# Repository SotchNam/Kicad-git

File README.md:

# Github tools used:
- *[KiCad-Diff](https://github.com/Gasman2014/KiCad-Diff)*: Provides side by side visualisation of each layer of the pcb between two commits, unable to do schematics it seems.
- *[Kiri](https://github.com/leoheck/kiri)*: Usefull tool that allows to see visualize diff of everything, in a web browser. Based on KiCad-Diff
- *[KiDiff](https://github.com/INTI-CMNB/KiDiff)*: A git plugin, opens a pdf every ``git diff`` run that shows overlays of changes. Simple.
- *[Board2Pdf](https://gitlab.com/dennevi/Board2Pdf)*: Plugin to generate pdf export of pcb layout, had an issue with python PyMuPDF. Can be used on cli, which is usefull to make it a commit git hook or automate actions.
- *[kicad render pcb](https://github.com/marketplace/actions/kicad-render-pcb)*: Github action tat develops a render of the pcb.
### Images

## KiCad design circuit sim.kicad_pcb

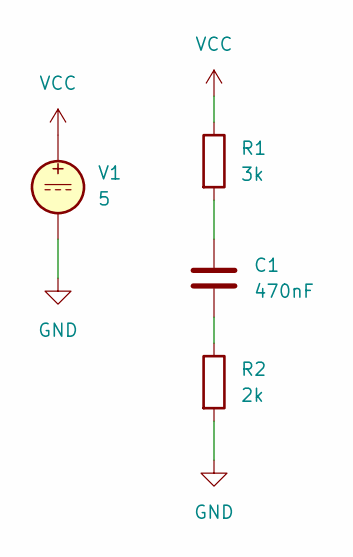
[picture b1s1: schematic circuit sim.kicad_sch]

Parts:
C1: 470nF; C_1206_3216Metric
R1: 3k; R_0603_1608Metric
R2: 2k; R_0603_1608Metric
V1: 5; PinHeader_1x02_P1.00mm_Vertical

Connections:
GND: R2.2, V1.2
unnamed: C1.1, R1.2
unnamed: C1.2, R2.1
VCC: R1.1, V1.1

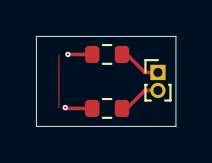
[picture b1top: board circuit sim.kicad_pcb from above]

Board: 2 copper layers, 7.8 x 5.0 mm, 4 parts (1 on the bottom side), 4 nets.

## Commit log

2024-08-15 git: added gitignore and ignored the ignorables
2024-08-16 changed stuff in circuit
2024-08-16 git: added readme to describe the git tools experience
2024-08-17 Added another tool
2024-08-19 Added yet another tool
2024-08-19 Added the pdf commit hook file
2024-08-19 Configured hook to also export pdf
2024-08-20 Added yet another tool fr
2024-08-20 Made a simple pcb
